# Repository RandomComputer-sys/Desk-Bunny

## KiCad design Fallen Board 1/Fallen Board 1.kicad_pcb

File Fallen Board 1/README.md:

The design for a PCB board that features an ESP32-S3-Wroom-1, a voltage regulator, an audio chip, pads for 7 servos, and pads for 2 smart LEDs. There is also a circit for cutting power from the battery when the ESP32 turns off using a MOSFET and transistor. This will be the brain for the entire project.

The board is 90mm x 59mm.

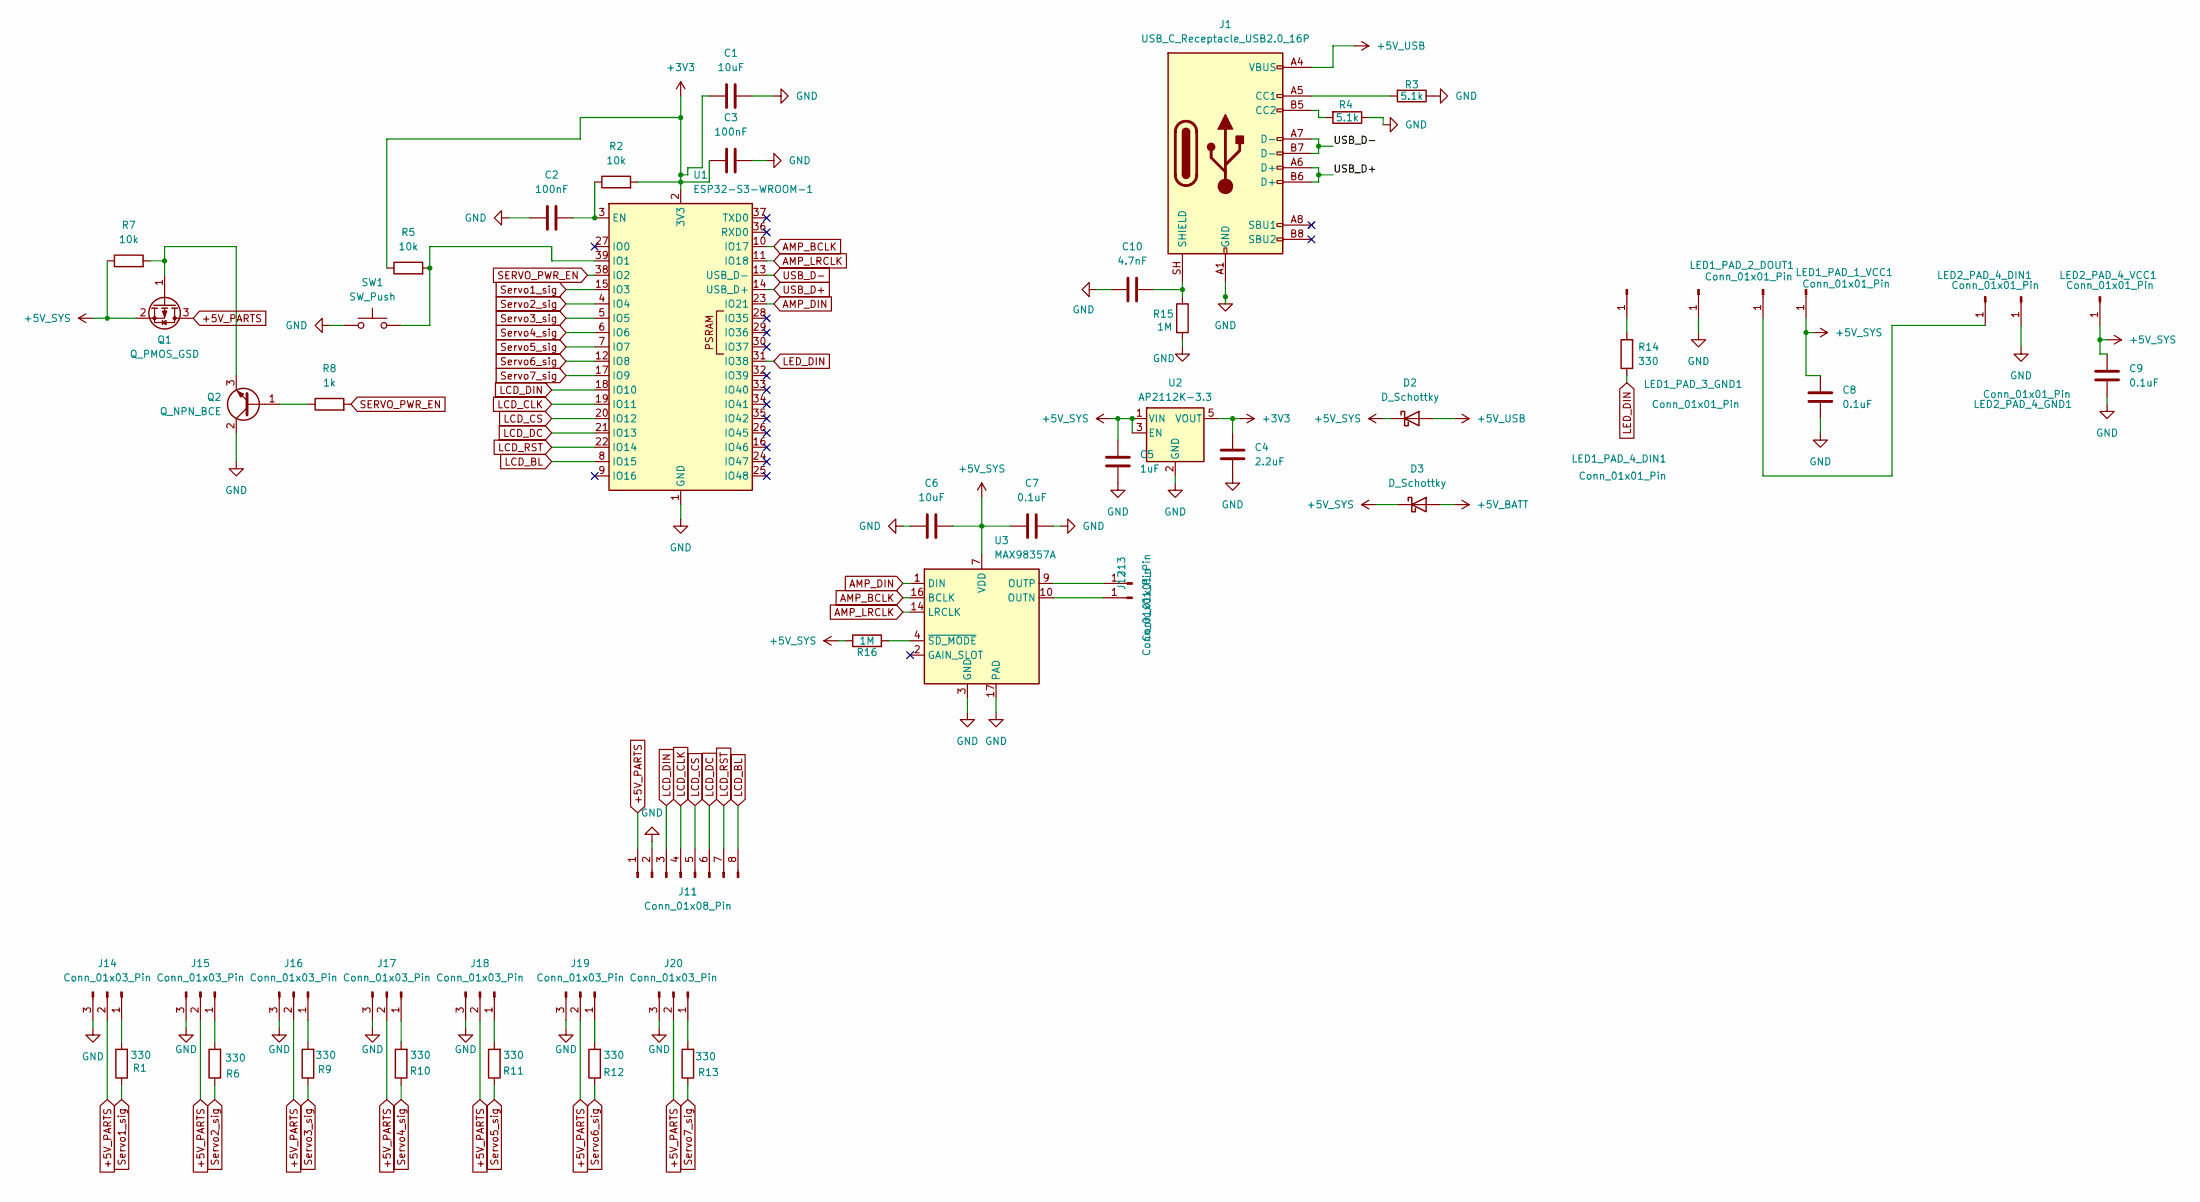
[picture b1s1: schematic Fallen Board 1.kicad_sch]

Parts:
C1, C6: 10uF; C_0603_1608Metric_Pad1.08x0.95mm_HandSolder
C2, C3: 100nF; C_0603_1608Metric_Pad1.08x0.95mm_HandSolder
C4: 2.2uF; C_0603_1608Metric_Pad1.08x0.95mm_HandSolder
C5: 1uF; C_0603_1608Metric_Pad1.08x0.95mm_HandSolder
C7, C8, C9: 0.1uF; C_0603_1608Metric_Pad1.08x0.95mm_HandSolder
C10: 4.7nF; C_0603_1608Metric_Pad1.08x0.95mm_HandSolder
D2, D3: D_Schottky; D_SOD-123
J1: USB_C_Receptacle_USB2.0_16P; USB_C_Receptacle_HRO_TYPE-C-31-M-12
J11: Conn_01x08_Pin; PinHeader_1x08_P2.54mm_Vertical
J12, J13: Conn_01x01_Pin; PinHeader_1x01_P2.54mm_Vertical
J14, J15, J16, J17, J18, J19, J20: Conn_01x03_Pin; PinHeader_1x03_P2.54mm_Vertical
LED1_PAD_1_VCC1, LED1_PAD_2_DOUT1, LED1_PAD_3_GND1, LED1_PAD_4_DIN1, LED2_PAD_4_DIN1, LED2_PAD_4_GND1, LED2_PAD_4_VCC1: Conn_01x01_Pin; PinHeader_1x01_P2.54mm_Vertical
Q1: Q_PMOS_GSD; SOT-23_Handsoldering
Q2: Q_NPN_BCE; SOT-23_Handsoldering
R1, R6, R9, R10, R11, R12, R13, R14: 330; R_0603_1608Metric_Pad0.98x0.95mm_HandSolder
R2, R5, R7: 10k; R_0603_1608Metric_Pad0.98x0.95mm_HandSolder
R3, R4: 5.1k; R_0603_1608Metric_Pad0.98x0.95mm_HandSolder
R8: 1k; R_0603_1608Metric_Pad0.98x0.95mm_HandSolder
R15, R16: 1M; R_0603_1608Metric_Pad0.98x0.95mm_HandSolder
SW1: SW_Push; SW_Push_1P1T_NO_E-Switch_TL3301NxxxxxG
U1: ESP32-S3-WROOM-1
U2: AP2112K-3.3; SOT-23-5
U3: MAX98357A; TQFN-16-1EP_3x3mm_P0.5mm_EP1.23x1.23mm

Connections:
+3V3: C1.2, C3.1, C4.2, R2.2, R5.1, U1.2 (3V3), U2.5 (VOUT)
+5V_BATT: D3.2 (A)
+5V_PARTS: J11.1, J14.2, J15.2, J16.2, J17.2, J18.2, J19.2, J20.2, Q1.3 (D)
+5V_SYS: C5.2, C6.2, C7.1, C8.1, C9.1, D2.1 (K), D3.1 (K), LED1_PAD_1_VCC1.1 (Pin_1_1), LED2_PAD_4_VCC1.1 (Pin_1_1), Q1.2 (S), R7.1, R16.1, U2.1 (VIN), U2.3 (EN), U3.7 (VDD), U3.8 (VDD)
+5V_USB: D2.2 (A), J1.A4 (VBUS), J1.A9 (VBUS), J1.B4 (VBUS), J1.B9 (VBUS)
AMP_BCLK: U1.10 (IO17), U3.16 (BCLK)
AMP_DIN: U1.23 (IO21), U3.1 (DIN)
AMP_LRCLK: U1.11 (IO18), U3.14 (LRCLK)
GND: C1.1, C2.1, C3.2, C4.1, C5.1, C6.1, C7.2, C8.2, C9.2, C10.2, J1.A1 (GND), J1.A12 (GND), J1.B1 (GND), J1.B12 (GND), J11.2, J14.3, J15.3, J16.3, J17.3, J18.3, J19.3, J20.3, LED1_PAD_3_GND1.1 (Pin_1_1), LED2_PAD_4_GND1.1 (Pin_1_1), Q2.2 (C), R3.1, R4.1, R15.2, SW1.1, U1.1 (GND), U1.40 (GND), U1.41 (GND), U2.2 (GND), U3.3 (GND), U3.11 (GND), U3.15 (GND), U3.17 (PAD)
LCD_BL: J11.8, U1.8 (IO15)
LCD_CLK: J11.4, U1.19 (IO11)
LCD_CS: J11.5, U1.20 (IO12)
LCD_DC: J11.6, U1.21 (IO13)
LCD_DIN: J11.3, U1.18 (IO10)
LCD_RST: J11.7, U1.22 (IO14)
LED_DIN: R14.1, U1.31 (IO38)
unnamed: J1.A5 (CC1), R3.2
unnamed: J1.B5 (CC2), R4.2
unnamed: C10.1, J1.SH (SHIELD), R15.1
unnamed: J12.1 (Pin_1_1), U3.10 (OUTN)
unnamed: J13.1 (Pin_1_1), U3.9 (OUTP)
unnamed: J14.1, R1.2
unnamed: J15.1, R6.2
unnamed: J16.1, R9.2
unnamed: J17.1, R10.2
unnamed: J18.1, R11.2
unnamed: J19.1, R12.2
unnamed: J20.1, R13.2
unnamed: LED1_PAD_2_DOUT1.1 (Pin_1_1), LED2_PAD_4_DIN1.1 (Pin_1_1)
unnamed: LED1_PAD_4_DIN1.1 (Pin_1_1), R14.2
unnamed: Q1.1 (G), Q2.3 (E), R7.2
unnamed: Q2.1 (B), R8.1
unnamed: C2.2, R2.1, U1.3 (EN)
unnamed: R5.2, SW1.2, U1.39 (IO1)
unnamed: R16.2, U3.4 (~SD_MODE)
SERVO_PWR_EN: R8.2, U1.38 (IO2)
Servo1_sig: R1.1, U1.15 (IO3)
Servo2_sig: R6.1, U1.4 (IO4)
Servo3_sig: R9.1, U1.5 (IO5)
Servo4_sig: R10.1, U1.6 (IO6)
Servo5_sig: R11.1, U1.7 (IO7)
Servo6_sig: R12.1, U1.12 (IO8)
Servo7_sig: R13.1, U1.17 (IO9)
USB_D+: J1.A6 (D+), J1.B6 (D+), U1.14 (USB_D+)
USB_D-: J1.A7 (D-), J1.B7 (D-), U1.13 (USB_D-)

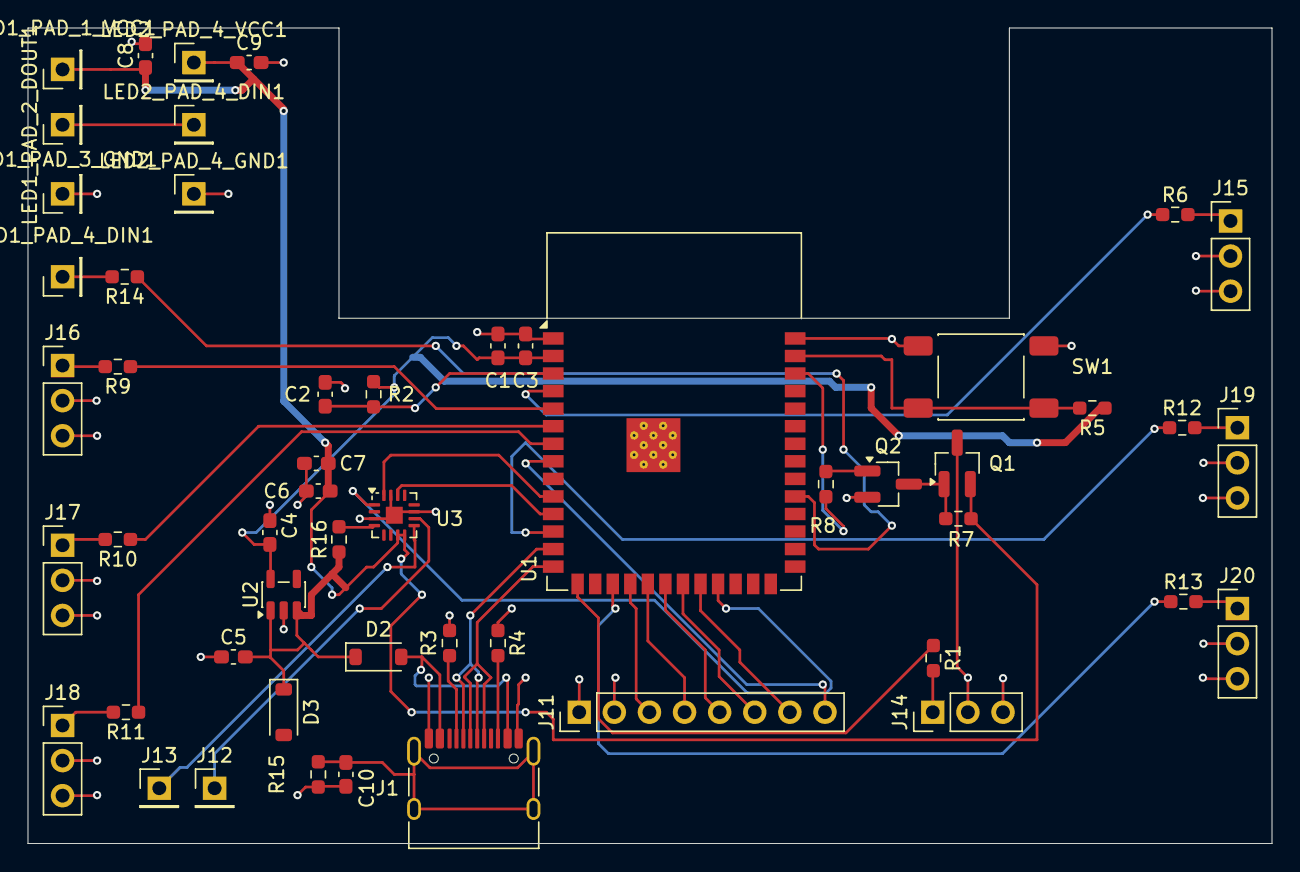
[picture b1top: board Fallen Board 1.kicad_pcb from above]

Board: 4 copper layers, 90.0 x 59.0 mm, 52 parts (0 on the bottom side), 44 nets.

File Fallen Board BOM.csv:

"Id";"Designator";"Footprint";"Quantity";"Designation";"Supplier and ref";
1;"C1, C6";"C_0603_1608Metric_Pad1.08x0.95mm_HandSolder";2;"10uF";;;
2;"C2, C3";"C_0603_1608Metric_Pad1.08x0.95mm_HandSolder";2;"100nF";;;
3;"C4";"C_0603_1608Metric_Pad1.08x0.95mm_HandSolder";1;"2.2uF";;;
4;"C5";"C_0603_1608Metric_Pad1.08x0.95mm_HandSolder";1;"1uF";;;
5;"C7, C8, C9";"C_0603_1608Metric_Pad1.08x0.95mm_HandSolder";3;"0.1uF";;;
6;"C10";"C_0603_1608Metric_Pad1.08x0.95mm_HandSolder";1;"4.7nF";;;
7;"D2, D3";"D_SOD-123";2;"D_Schottky";;;
8;"J1";"USB_C_Receptacle_HRO_TYPE-C-31-M-12";1;"USB_C_Receptacle_USB2.0_16P";;;
9;"J11";"PinHeader_1x08_P2.54mm_Vertical";1;"Conn_01x08_Pin";;;
10;"J12, J13, LED1_PAD_1_VCC1, LED1_PAD_2_DOUT1, LED1_PAD_3_GND1, LED1_PAD_4_DIN1, LED2_PAD_4_DIN1, LED2_PAD_4_GND1, LED2_PAD_4_VCC1";"PinHeader_1x01_P2.54mm_Vertical";9;"Conn_01x01_Pin";;;
11;"J14, J15, J16, J17, J18, J19, J20";"PinHeader_1x03_P2.54mm_Vertical";7;"Conn_01x03_Pin";;;
12;"Q1";"SOT-23_Handsoldering";1;"Q_PMOS_GSD";;;
13;"Q2";"SOT-23_Handsoldering";1;"Q_NPN_BCE";;;
14;"R1, R6, R9, R10, R11, R12, R13, R14";"R_0603_1608Metric_Pad0.98x0.95mm_HandSolder";8;"330";;;
15;"R2, R5, R7";"R_0603_1608Metric_Pad0.98x0.95mm_HandSolder";3;"10k";;;
16;"R3, R4";"R_0603_1608Metric_Pad0.98x0.95mm_HandSolder";2;"5.1k";;;
17;"R8";"R_0603_1608Metric_Pad0.98x0.95mm_HandSolder";1;"1k";;;
18;"R15, R16";"R_0603_1608Metric_Pad0.98x0.95mm_HandSolder";2;"1M";;;
19;"SW1";"SW_Push_1P1T_NO_E-Switch_TL3301NxxxxxG";1;"SW_Push";;;
20;"U1";"ESP32-S3-WROOM-1";1;"ESP32-S3-WROOM-1";;;
21;"U2";"SOT-23-5";1;"AP2112K-3.3";;;
22;"U3";"TQFN-16-1EP_3x3mm_P0.5mm_EP1.23x1.23mm";1;"MAX98357A";;;
